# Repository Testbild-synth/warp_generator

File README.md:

#  Warp Drive Sound Generator

Space. the final frontier. tbd.

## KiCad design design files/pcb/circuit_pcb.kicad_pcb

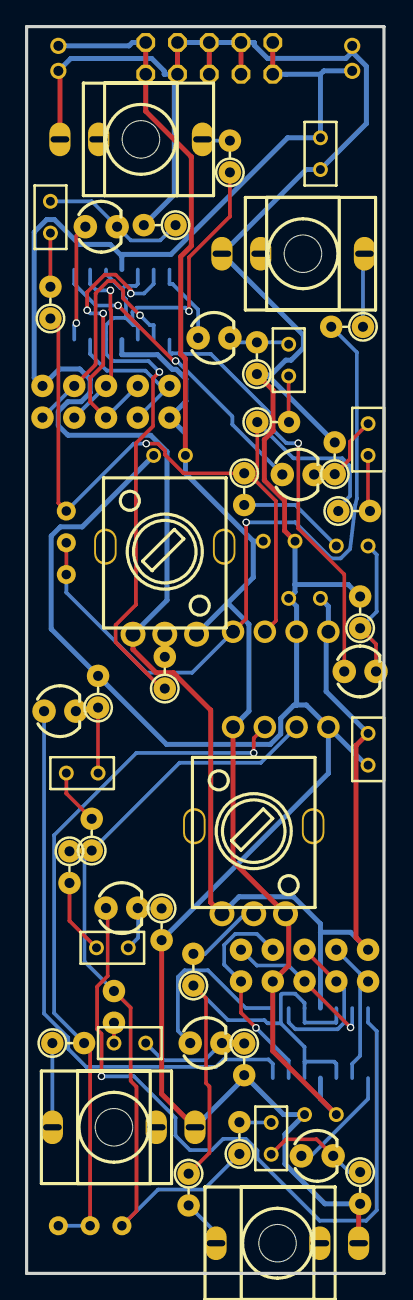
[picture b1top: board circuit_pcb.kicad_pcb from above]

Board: 2 copper layers, 28.6 x 99.7 mm, 68 parts (0 on the bottom side), 47 nets.

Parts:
C1, C3, C5, C9, C10, C12, C13, C14: 1u; RAD-0.1
C2, C4, C6, C7, C8, C11: 100n; RAD-0.1
C15, C16: 10u; CAP-D5.0-F2.0
ENERGY1, ENERGY2: 10k; R09-5KΩ
EP1: EURORACK_POWERHEADER_V2; EURORACK_POWER_V2
GAIN1, GAIN2: 10k; TRIMPOT
J1: O1; THONKICONN_1
J2: O2; THONKICONN_1
J3: CV1; THONKICONN_1
J4: CV2; THONKICONN_1
LED1, LED3, LED5, LED7: LED_FAST_3mm; LED3MM
LED2, LED4, LED6, LED8: LED_SLOW_3mm; LED3MM
R1, R4, R5, R10, R12, R19, R21, R27, R28, R32: 4k7; 1/4W-RESISTOR-VERTICAL
R2, R6, R9, R11, R14, R16, R17, R22, R24, R25, R29, R30: 1k; 1/4W-RESISTOR-VERTICAL
R3, R7, R8, R13, R15, R18, R20, R23, R26, R31: 10k; 1/4W-RESISTOR-VERTICAL
U1, U2: TL074; SOIC14N
U3: TL072IP; PDIP-8_L10.2-W5.9-P2.54-LS7.6-BL

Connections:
+12V: C2.2, C4.2, C7.2, C15.1, ENERGY1.3, ENERGY2.3, EP1.12, R1.2, R4.2, U1.4, U2.4, U3.8
-12V: C6.2, C8.2, C11.2, C16.2, ENERGY1.1, ENERGY2.1, EP1.-12, R28.1, R32.1, U1.11, U2.11, U3.4
C1_1: C1.1, R3.2
C1_2: C1.2, LED1.2, R2.1
C3_1: C3.1, R7.2
C3_2: C3.2, LED2.2, R6.1
C5_1: C5.1, R8.2
C5_2: C5.2, LED3.2, R11.2
C9_1: C9.1, R15.2
C9_2: C9.2, LED4.2, R14.1
C10_1: C10.1, R18.2
C10_2: C10.2, LED5.2, R17.1
C12_1: C12.1, R23.2
C12_2: C12.2, LED6.2, R22.1
C13_1: C13.1, R26.2
C13_2: C13.2, LED7.2, R25.1
C14_1: C14.1, R31.2
C14_2: C14.2, LED8.2, R30.1
GND: C2.1, C4.1, C6.1, C7.1, C8.1, C11.1, C15.2, C16.1, EP1.GND0, EP1.GND1, EP1.GND2, EP1.GND3, EP1.GND4, EP1.GND5, J1.1, J2.1, J3.1, J4.1, R2.2, R6.2, R11.1, R14.2, R17.2, R22.2, R25.2, R30.2, U3.3, U3.5
R1_1: R1.1, R5.2, U1.6
R4_1: R4.1, R10.2, U2.6
R5_1: R5.1, R12.2, U1.13
R9_1: J1.3, R9.1
R10_1: R10.1, R19.2, U2.13
R12_1: R12.1, R21.2, U1.9
R13_2: ENERGY1.2, R13.2
R16_1: J2.3, R16.1
R19_1: R19.1, R27.2, U2.9
R20_1: R20.1, R29.1, U2.3, U2.5, U2.10, U2.12
R20_2: ENERGY2.2, R20.2
R21_1: R21.1, R28.2, U1.2
R24_1: R13.1, R24.1, U1.3, U1.5, U1.10, U1.12
R24_2: J3.3, R24.2
R27_1: R27.1, R32.2, U2.2
R29_2: J4.3, R29.2
U1_1: LED7.1, U1.1
U1_7: LED1.1, U1.7
U1_8: LED5.1, U1.8
U1_14: LED3.1, U1.14
U2_1: LED8.1, U2.1
U2_7: LED2.1, U2.7
U2_8: LED6.1, U2.8
U2_14: LED4.1, U2.14
U3_1: GAIN1.2, GAIN1.3, R9.2, U3.1
U3_2: GAIN1.1, R3.1, R8.1, R18.1, R26.1, U3.2
U3_6: GAIN2.1, R7.1, R15.1, R23.1, R31.1, U3.6
U3_7: GAIN2.2, GAIN2.3, R16.2, U3.7

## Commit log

2022-12-04 upload files
